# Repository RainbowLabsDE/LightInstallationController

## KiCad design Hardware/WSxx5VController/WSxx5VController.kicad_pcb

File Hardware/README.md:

# LightInstallationController

Hardware noch in Entstehung keins der boardsa ktuell in betrieb genommen.

## Main Controller

- STM32
- 8x RS485 Out
- Ethernet 
- Oled
- User Input Button / rotery Encoder ?
- Power Input 
- Digital Out to Control External Power Supply

## StripController

- CH32V003
- 5x 10A N-Channel Mosfet Output
- 5-24V Input DCDC Converter
- RS485 Tranciver

## CCController

- CH32V003 
- 5x DCDC buck CC Outputs
- 5-24V Input DCDC Converter
- RS485 Tranciver

## WSxxController

- CH32V003
- 5-24V Input DCDC Converter
- RS485 Tranciver
- P-Channel Fet to PowerOff WsxxLeds

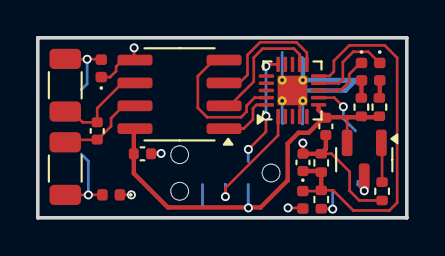
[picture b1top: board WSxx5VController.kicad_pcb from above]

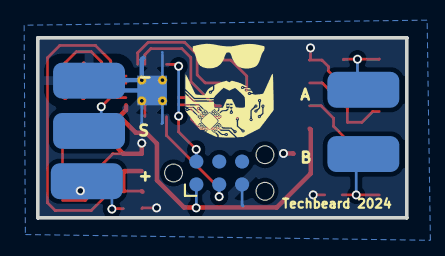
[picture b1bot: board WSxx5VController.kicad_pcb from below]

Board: 2 copper layers, 20.5 x 10.0 mm, 25 parts (6 on the bottom side), 20 nets.

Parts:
C3, C4, C5: 100n; C_0402_1005Metric
D2: 5,1V; D_0402_1005Metric
D3: S1; LED_0402_1005Metric
D4: S2; LED_0402_1005Metric
D5, D6: D_TVS; D_0402_1005Metric
IC1: CH32V003F4U6; QFN-20-1EP_3x3mm_P0.4mm_EP1.65x1.65mm_ThermalVias
J1: TagConnect; Tag-Connect_TC2030-IDC-NL_2x03_P1.27mm_Vertical
J2, J3, J4, J5, J6: Conn_01x01_Socket; SolderWirePad_1x01_SMD_2x4mm
Q1: AO3401A; SOT-23
R1: 1M; R_0402_1005Metric
R2: 270k; R_0402_1005Metric
R4, R5: 1k; R_0402_1005Metric
R6: 120; C_0402_1005Metric
R8: 100k; R_0402_1005Metric
R9, R10: 10; R_1206_3216Metric
U1: MAX485E; SOIC-8_3.9x4.9mm_P1.27mm

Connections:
+5V: C3.1, C5.1, IC1.6 (VDD), J1.1, Q1.2 (S), R4.1, R5.1, U1.8 (VCC)
A: R6.2, R10.1, U1.6 (A)
B: R6.1, R9.1, U1.7 (B)
GND: C3.2, C4.2, C5.2, D2.2 (A), D5.1 (A1), D6.1 (A1), IC1.4 (Vss), IC1.21 (Vss_Pad), J1.5, J3.1, R2.2, R8.2, U1.5 (GND)
NRST: IC1.1 (PD7/NRST), J1.3
unnamed: D3.2 (A), R4.2
unnamed: D4.2 (A), R5.2
unnamed: D5.2 (A2), J4.1, R9.2
unnamed: D6.2 (A2), J5.1, R10.2
unnamed: Q1.1 (G), R8.1
SWD: IC1.15 (PD1), J1.2
StateLed0: D4.1 (K), IC1.8 (PC1)
StateLed1: D3.1 (K), IC1.9 (PC2)
U2_DE: IC1.11 (PC4), U1.3 (DE)
U2_DI: IC1.19 (PD5), U1.4 (DI)
U2_RE: IC1.12 (PC5), U1.2 (~RE)
U2_RO: IC1.20 (PD6), U1.1 (RO)
VCC: J2.1, Q1.3 (D), R1.1
Voltage: C4.1, D2.1 (K), IC1.10 (PC3), R1.2, R2.1
WSxx: IC1.7 (PC0), J6.1

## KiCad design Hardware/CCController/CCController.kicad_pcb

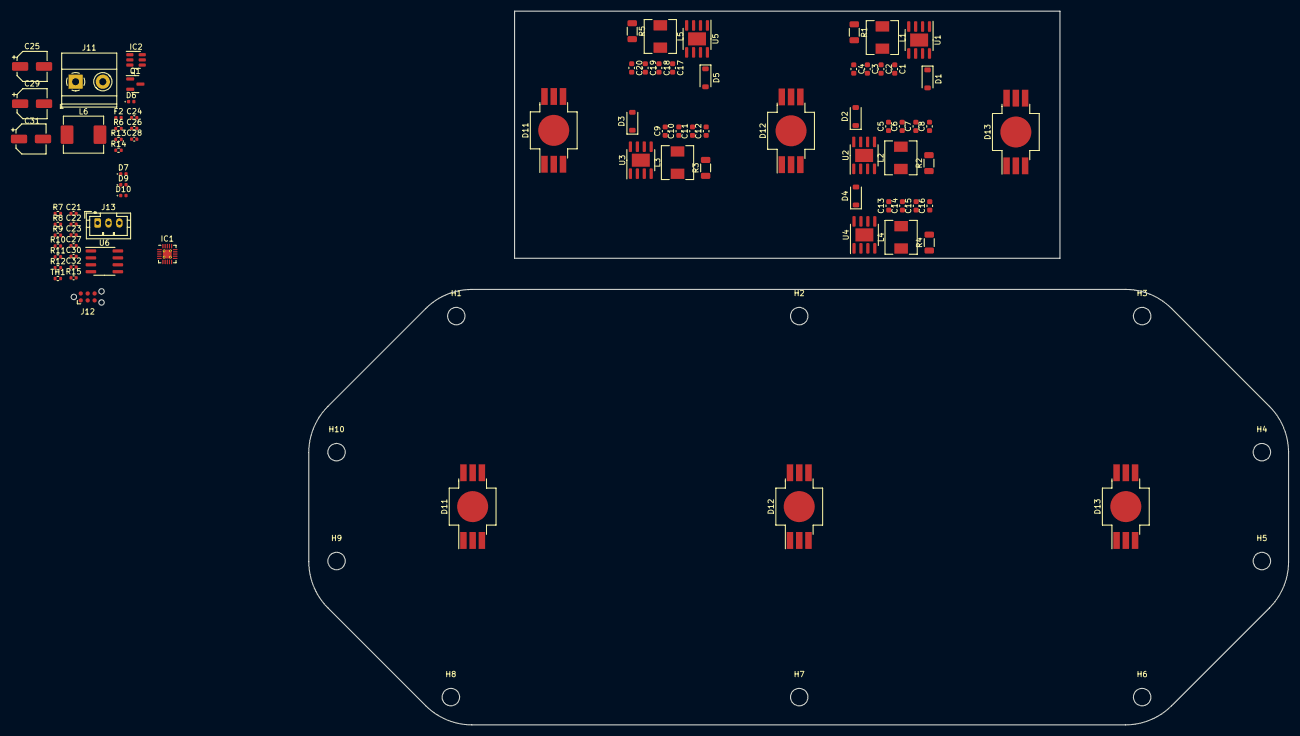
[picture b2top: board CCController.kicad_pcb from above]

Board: 2 copper layers, 180.0 x 131.1 mm, 92 parts (0 on the bottom side), 55 nets, no tracks yet.

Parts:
C1, C5, C9, C13, C17: 1n; C_0603_1608Metric
C2, C4, C6, C8, C10, C12, C14, C16, C18, C20: 1u; C_0603_1608Metric
C3, C7, C11, C15, C19: 4u7; C_0603_1608Metric
C21, C22: C; C_0402_1005Metric
C23, C24, C26, C27, C28, C30, C32: 100n; C_0402_1005Metric
C25: 47u; CP_Elec_5x5.4
C29, C31: 22u; CP_Elec_5x5.4
D1, D2, D3, D4, D5: 40V 1A Schottky; D_SOD-123
D6: 15V; D_0402_1005Metric
D7, D9, D10: LED; LED_0402_1005Metric
D11, D11#2, D12, D12#2, D13, D13#2: LED_RGB; LED_RGB_Getian_GT-P6PRGB4303
F2: 0,2A; Fuse_0402_1005Metric
H1, H2, H3, H4, H5, H6, H7, H8, H9, H10: MountingHole; MountingHole_3.2mm_M3
IC1: CH32V003F4U6; QFN-20-1EP_3x3mm_P0.4mm_EP1.65x1.65mm_ThermalVias
IC2: RY8310; SOT-23-6
J11: Conn_01x02_Pin; TerminalBlock_Phoenix_MKDS-1,5-2_1x02_P5.00mm_Horizontal
J12: TagConnect; Tag-Connect_TC2030-IDC-NL_2x03_P1.27mm_Vertical
J13: Conn_01x03_Socket; JST_PH_B3B-PH-K_1x03_P2.00mm_Vertical
L1, L2, L3, L4, L5: 10u; L_Chilisin_BMRA00050520
L6: 4.7u; L_Abracon_ASPI-0630LR
Q1: AO3401A; SOT-23
R1, R2, R3, R4, R5: 0R68; R_1206_3216Metric
R6, R11: 100k; R_0402_1005Metric
R7: 1M; R_0402_1005Metric
R8: 270k; R_0402_1005Metric
R9, R10, R12: 1k; R_0402_1005Metric
R13: 52.50 k; R_0402_1005Metric
R14: 10k; R_0402_1005Metric
R15: 1k; C_0402_1005Metric
TH1: Thermistor_NTC; R_0402_1005Metric
U1, U2, U3, U4, U5: BP1808; SOIC-8-1EP_3.9x4.9mm_P1.27mm_EP2.41x3.3mm
U6: MAX485E; SOIC-8_3.9x4.9mm_P1.27mm

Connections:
+5V: C23.1, C28.1, C29.1, C31.1, C32.1, IC1.6 (VDD), J12.1, L6.2, R9.1, R10.1, R11.1, R12.1, R13.2, U6.8 (VCC)
A+: R5.2, U5.8 (CS)
A-: C20.1, L5.2
B: IC1.7 (PC0), U3.3 (DIM)
B+: R3.2, U3.8 (CS)
B-: C12.1, L3.2
G: IC1.14 (PC7), U2.3 (DIM)
G+: R2.2, U2.8 (CS)
G-: C8.1, L2.2
GND: C1.2, C2.2, C3.2, C5.2, C6.2, C7.2, C9.2, C10.2, C11.2, C13.2, C14.2, C15.2, C17.2, C18.2, C19.2, C21.2, C22.2, C23.2, C24.2, C25.2, C27.2, C28.2, C29.2, C30.2, C31.2, C32.2, D7.1 (K), IC1.4 (Vss), IC1.21 (Vss_Pad), IC2.2 (GND), J11.2, J12.5, J13.3, R6.2, R8.2, R14.1, TH1.2, U1.4 (GND), U2.4 (GND), U3.4 (GND), U4.4 (GND), U5.4 (GND), U6.5 (GND)
NRST: IC1.1 (PD7/NRST), J12.3
unnamed: D1.2 (A), L1.1, U1.5 (SW)
unnamed: D2.2 (A), L2.1, U2.5 (SW)
unnamed: D3.2 (A), L3.1, U3.5 (SW)
unnamed: D4.2 (A), L4.1, U4.5 (SW)
unnamed: D5.2 (A), L5.1, U5.5 (SW)
unnamed: D6.2 (A), Q1.1 (G), R6.1
unnamed: C24.1, C25.1, D6.1 (K), IC2.4 (EN), IC2.5 (IN), Q1.2 (S)
unnamed: D7.2 (A), R9.2
unnamed: D9.2 (A), R10.2
unnamed: D10.2 (A), R12.2
unnamed: C26.1, IC2.1 (CB)
unnamed: IC2.3 (FB), R13.1, R14.2
unnamed: C26.2, IC2.6 (SW), L6.1
unnamed: F2.1, J11.1
unnamed: F2.2, Q1.3 (D)
unnamed: C1.1, U1.2 (COMP)
unnamed: C2.1, U1.6 (VDD)
unnamed: C5.1, U2.2 (COMP)
unnamed: C6.1, U2.6 (VDD)
unnamed: C9.1, U3.2 (COMP)
unnamed: C10.1, U3.6 (VDD)
unnamed: C13.1, U4.2 (COMP)
unnamed: C14.1, U4.6 (VDD)
unnamed: C17.1, U5.2 (COMP)
unnamed: C18.1, U5.6 (VDD)
R: IC1.13 (PC6), U1.3 (DIM)
R+: R1.2, U1.8 (CS)
R-: C4.1, L1.2
RA: J13.1, R15.2, U6.6 (A)
RB: J13.2, R15.1, U6.7 (B)
SWD: IC1.15 (PD1), J12.2
StateLed0: D10.1 (K), IC1.8 (PC1)
StateLed1: D9.1 (K), IC1.9 (PC2)
Temp: C30.1, IC1.16 (PD2), R11.2, TH1.1
U2_DE: IC1.11 (PC4), U6.3 (DE)
U2_DI: IC1.19 (PD5), U6.4 (DI)
U2_RE: IC1.12 (PC5), U6.2 (~RE)
U2_RO: IC1.20 (PD6), U6.1 (RO)
VCC: C3.1, C4.2, C7.1, C8.2, C11.1, C12.2, C15.1, C16.2, C19.1, C20.2, D1.1 (K), D2.1 (K), D3.1 (K), D4.1 (K), D5.1 (K), R1.1, R2.1, R3.1, R4.1, R5.1, R7.1, U1.7 (VOUT), U2.7 (VOUT), U3.7 (VOUT), U4.7 (VOUT), U5.7 (VOUT)
Voltage: C27.1, IC1.10 (PC3), R7.2, R8.1
W: IC1.17 (PD3), U4.3 (DIM)
W+: R4.2, U4.8 (CS)
W-: C16.1, L4.2
WW: IC1.18 (PD4), U5.3 (DIM)

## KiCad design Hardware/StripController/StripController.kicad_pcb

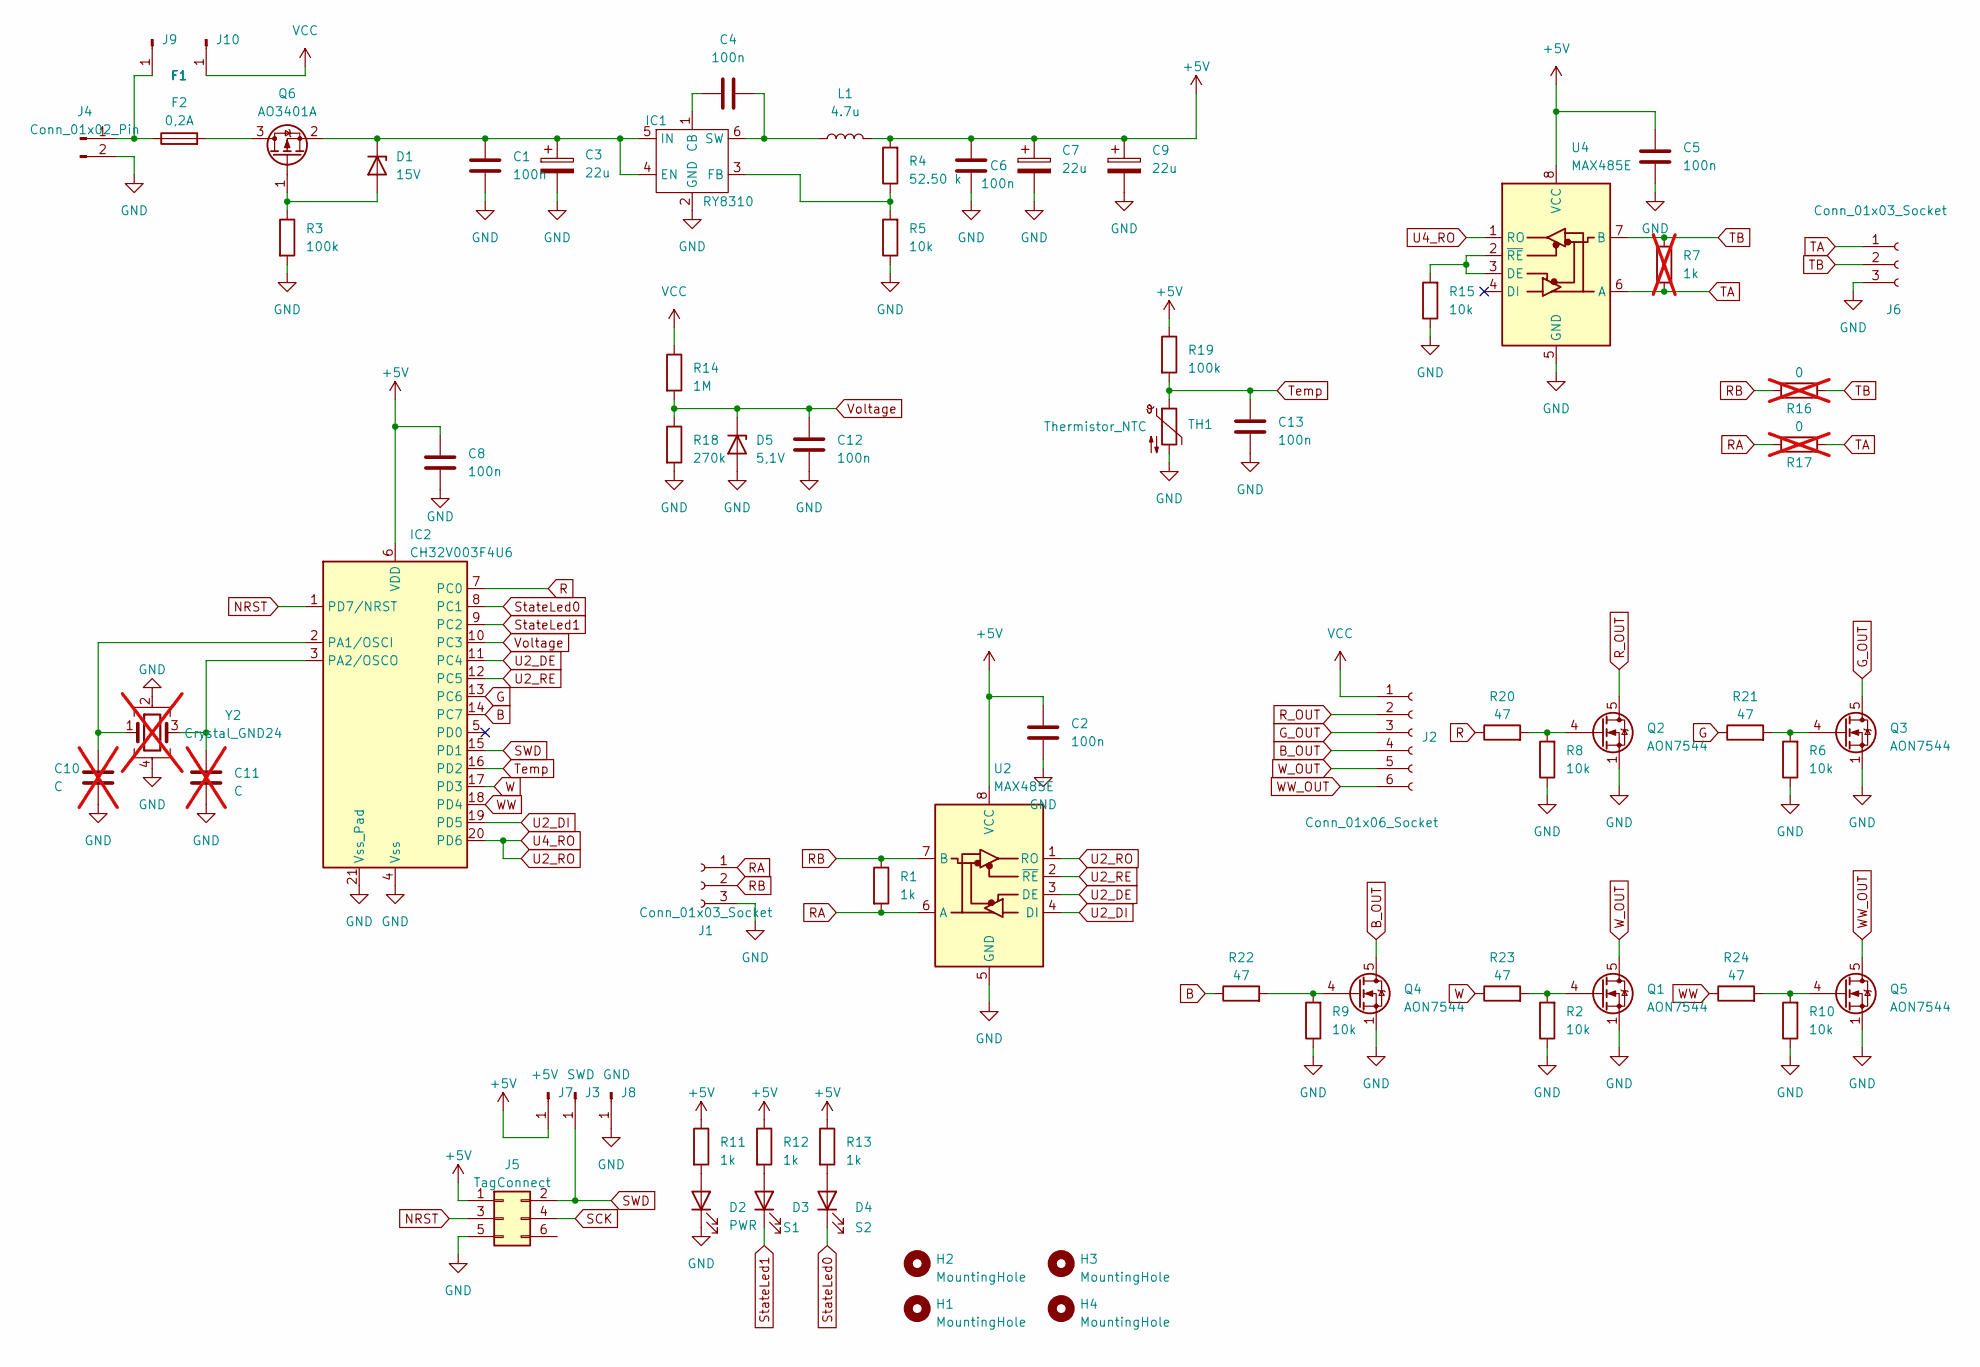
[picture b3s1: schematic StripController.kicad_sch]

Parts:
C1, C2, C4, C5, C6, C8, C12, C13: 100n; C_0402_1005Metric
C3, C7, C9: 22u; CP_Elec_5x5.4
C10, C11: C; C_0402_1005Metric; not fitted
D1: 15V; D_SOD-323
D2: PWR; LED_0603_1608Metric
D3: S1; LED_0603_1608Metric
D4: S2; LED_0603_1608Metric
D5: 5,1V; D_SOD-323
F2: 0,2A; Fuse_0402_1005Metric
H1, H2, H3, H4: MountingHole; MountingHole_3.2mm_M3
IC1: RY8310; SOT-23-6
IC2: CH32V003F4U6; QFN-20-1EP_3x3mm_P0.4mm_EP1.65x1.65mm_ThermalVias
J1, J6: Conn_01x03_Socket; JST_PH_B3B-PH-K_1x03_P2.00mm_Vertical
J2: Conn_01x06_Socket; TerminalBlock_Phoenix_MKDS-1,5-6_1x06_P5.00mm_Horizontal
J3: SWD; TestPoint_Pad_1.5x1.5mm
J4: Conn_01x02_Pin; TerminalBlock_Phoenix_MKDS-1,5-2_1x02_P5.00mm_Horizontal
J5: TagConnect; Tag-Connect_TC2030-IDC-NL_2x03_P1.27mm_Vertical
J7: +5V; TestPoint_Pad_1.5x1.5mm
J8: GND; TestPoint_Pad_1.5x1.5mm
J9, J10: F1; Fuseholder C3130
L1: 4.7u; L_0630
Q1, Q2, Q3, Q4, Q5: AON7544
Q6: AO3401A; TSOT-23
R1: 1k; C_0402_1005Metric
R2, R5, R6, R8, R9, R10, R15: 10k; R_0402_1005Metric
R3, R19: 100k; R_0402_1005Metric
R4: 52.50 k; R_0402_1005Metric
R7: 1k; C_0402_1005Metric; not fitted
R11, R12, R13: 1k; R_0402_1005Metric
R14: 1M; R_0402_1005Metric
R16, R17: 0; R_0402_1005Metric; not fitted
R18: 270k; R_0402_1005Metric
R20, R21, R22, R23, R24: 47; R_0402_1005Metric
TH1: Thermistor_NTC; R_0402_1005Metric
U2, U4: MAX485E; SOIC-8_3.9x4.9mm_P1.27mm
Y2: Crystal_GND24; Crystal_SMD_3225-4Pin_3.2x2.5mm; not fitted

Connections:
B: IC2.14 (PC7), R22.1
B_OUT: J2.4, Q4.5 (D)
G: IC2.13 (PC6), R21.1
GND: C1.2, C2.2, C3.2, C5.2, C6.2, C7.2, C8.2, C9.2, C10.2, C11.2, C12.2, C13.2, D2.1 (K), D5.2 (A), IC1.2 (GND), IC2.4 (Vss), IC2.21 (Vss_Pad), J1.3, J4.2, J5.5, J6.3, J8.1, Q1.1 (S), Q1.2 (S), Q1.3 (S), Q2.1 (S), Q2.2 (S), Q2.3 (S), Q3.1 (S), Q3.2 (S), Q3.3 (S), Q4.1 (S), Q4.2 (S), Q4.3 (S), Q5.1 (S), Q5.2 (S), Q5.3 (S), R2.1, R3.2, R5.1, R6.1, R8.1, R9.1, R10.1, R15.1, R18.2, TH1.2, U2.5 (GND), U4.5 (GND), Y2.2, Y2.4
G_OUT: J2.3, Q3.5 (D)
NRST: IC2.1 (PD7/NRST), J5.3
unnamed: D1.2 (A), Q6.1 (G), R3.1
unnamed: C1.1, C3.1, D1.1 (K), IC1.4 (EN), IC1.5 (IN), Q6.2 (S)
unnamed: D2.2 (A), R11.2
unnamed: D3.2 (A), R12.2
unnamed: D4.2 (A), R13.2
unnamed: C4.1, IC1.1 (CB)
unnamed: IC1.3 (FB), R4.1, R5.2
unnamed: C4.2, IC1.6 (SW), L1.1
unnamed: C10.1, IC2.2 (PA1/OSCI), Y2.1
unnamed: C11.1, IC2.3 (PA2/OSCO), Y2.3
unnamed: F2.1, J4.1, J9.1
unnamed: Q1.4 (G), R2.2, R23.2
unnamed: Q2.4 (G), R8.2, R20.2
unnamed: Q3.4 (G), R6.2, R21.2
unnamed: Q4.4 (G), R9.2, R22.2
unnamed: Q5.4 (G), R10.2, R24.2
unnamed: F2.2, Q6.3 (D)
unnamed: R15.2, U4.2 (~RE), U4.3 (DE)
R: IC2.7 (PC0), R20.1
RA: J1.1, R1.2, R17.1, U2.6 (A)
RB: J1.2, R1.1, R16.2, U2.7 (B)
R_OUT: J2.2, Q2.5 (D)
SCK: J5.4
SWD: IC2.15 (PD1), J3.1, J5.2
StateLed0: D4.1 (K), IC2.8 (PC1)
StateLed1: D3.1 (K), IC2.9 (PC2)
TA: J6.1, R7.2, R17.2, U4.6 (A)
TB: J6.2, R7.1, R16.1, U4.7 (B)
Temp: C13.1, IC2.16 (PD2), R19.2, TH1.1
U2_DE: IC2.11 (PC4), U2.3 (DE)
U2_DI: IC2.19 (PD5), U2.4 (DI)
U2_RE: IC2.12 (PC5), U2.2 (~RE)
U2_RO: IC2.20 (PD6), U2.1 (RO), U4.1 (RO)
W: IC2.17 (PD3), R23.1
WW: IC2.18 (PD4), R24.1
WW_OUT: J2.6, Q5.5 (D)
W_OUT: J2.5, Q1.5 (D)

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
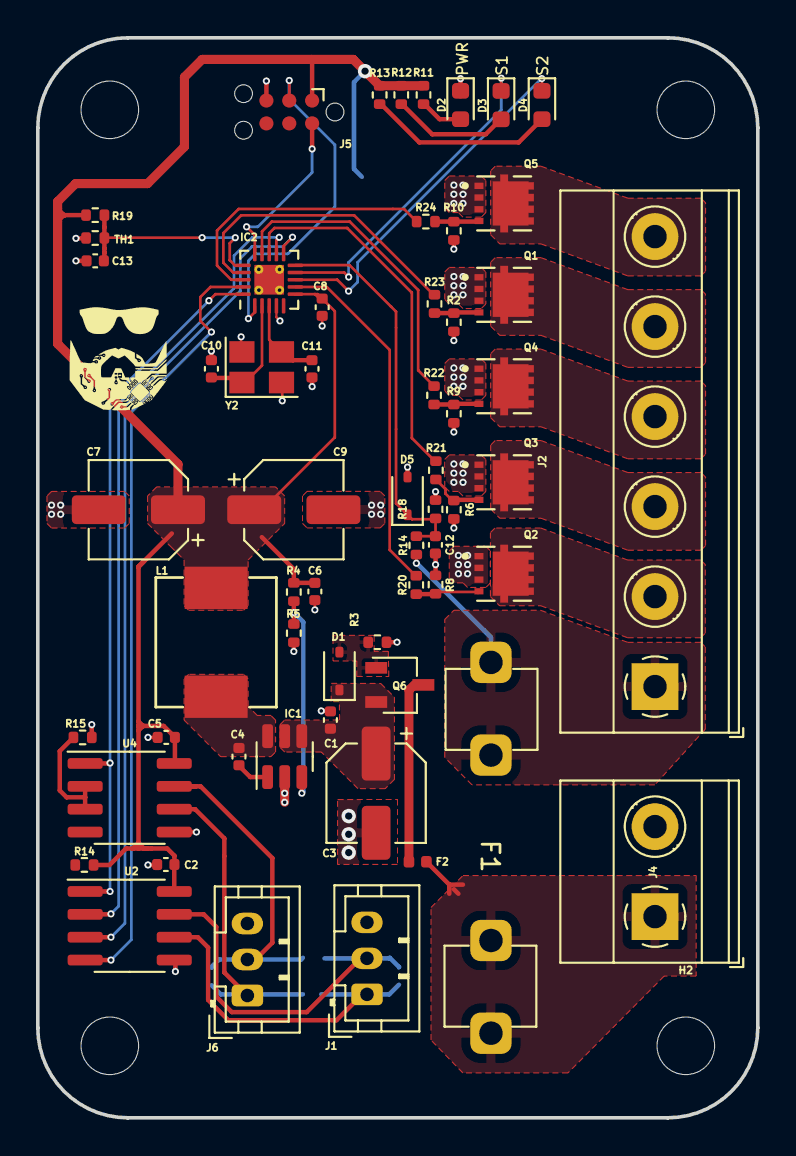
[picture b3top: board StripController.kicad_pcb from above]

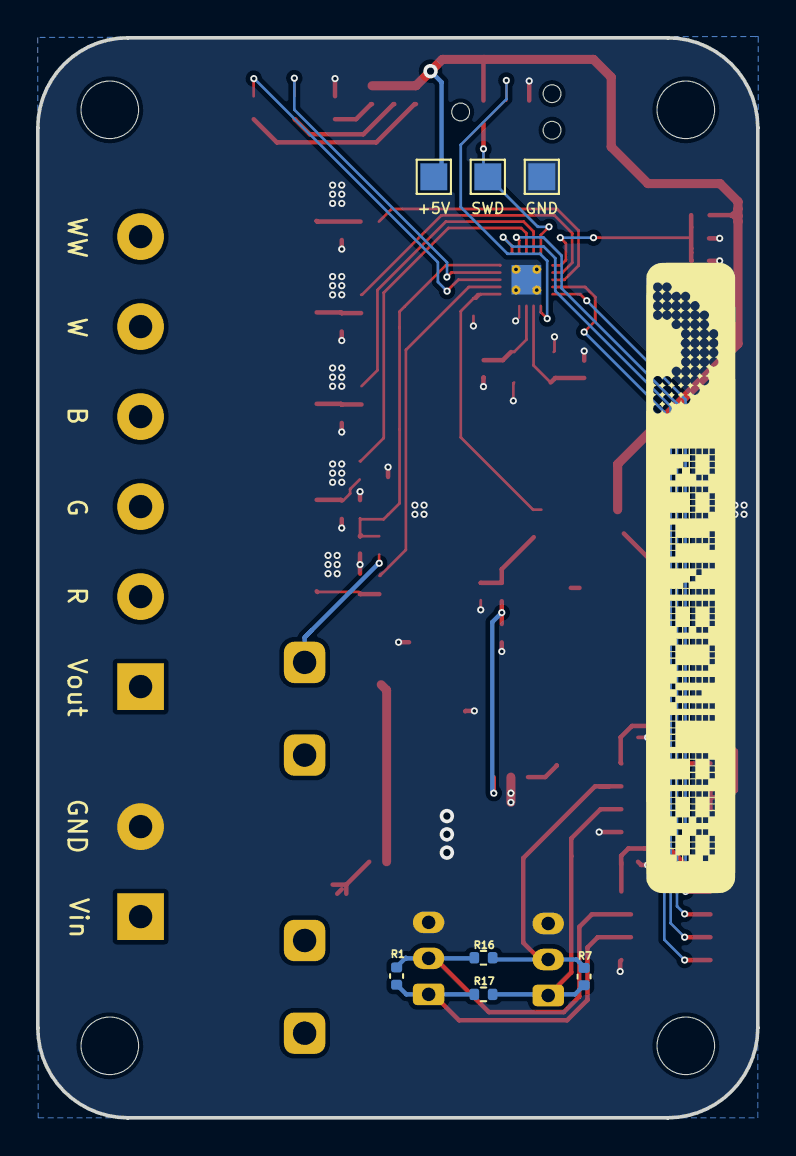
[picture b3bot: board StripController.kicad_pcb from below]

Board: 2 copper layers, 40.0 x 60.0 mm, 71 parts (7 on the bottom side), 45 nets.

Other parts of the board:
R14#2: 1M; R_0402_1005Metric

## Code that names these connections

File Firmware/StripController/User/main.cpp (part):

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vu8 val;
Config config;

// R  - T1CH3 - PC0
// G  - T1CH1 - PC6 | WS2812 DOUT
// B  - T1CH2 - PC7
// W  - T1CH4 - PD3
// WW - T2CH2 - PD4
// TX - PD5
// RX - PD6
// LED1 - PC1
// LED2 - PC2
// DE - PC4
// RE - PC5 (active low)
// VBUS - PC3 - A?? (wrong pin?) -> PA2 (A0)
// TEMP - PD2 - A3

#define PIN_LED1        GPIOC, GPIO_Pin_1
#define PIN_LED2        GPIOC, GPIO_Pin_2
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 */
void TIM1_PWMOut_Init(u16 arr, u16 psc, u16 ccp) {
    RCC_APB2PeriphClockCmd(RCC_APB2Periph_AFIO, ENABLE);
    GPIO_PinRemapConfig(GPIO_PartialRemap1_TIM1, ENABLE); // CH1-4: PC6, PC7, PC0, PD3

    GPIO_InitTypeDef GPIO_InitStructure = {0};
    TIM_OCInitTypeDef TIM_OCInitStructure = {0};
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
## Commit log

2023-02-15 add Hardware files
2023-02-15 initialize CH32V003 MounRiver project
2023-02-15 add PWM example
2023-02-15 enable other 3 PWM channels on TIM1 and remap pins
    Remapping doesn't work for some reason, still outputting on default pins
2023-02-15 fix pin remapping (AFIO clk needs to be enabled)
2023-02-15 test reading chip UID
2023-02-16 convert project to C++
2023-02-16 add FW/SC readme
2023-02-16 begin implementing UART DMA
2023-02-16 move UART to separate file
    the structure doesn't quite feel right tho
2023-02-16 implement better SysTick timing functions
2023-02-16 try to optimize calculation time of micros()
    but there is another multiply which I can't easily get rid of
2023-02-16 fix longer delays not working
2023-02-16 implement getUID
2023-02-20 edit pcb desine
2023-02-26 add CCController
2023-03-07 UART implement readBytes
2023-03-07 begin with UART protocol implementation
    WIP, not working
2023-03-10 dry-implement more of the RBLB protocol
2023-03-11 edit Strip controller and buy first batch
2023-03-23 GPIO config and further RBLB development
2023-03-24 implement ADC DMA reading
2023-04-06 add code for test host for RBLB
2023-04-06 basic communication between RBLB host and nodes
2023-04-06 fix host not receiving packets
2023-08-07 auto discovery proof of concept working
2023-11-01 fix discovery algorithm
2023-11-01 fix RS485 not working (GPIOs not initialized)
2024-04-03 implement building via PlatformIO
2024-04-03 implement config storage in custom user option bytes
2024-04-04 add ability to disable debug prints
2024-04-05 add Files
2024-04-06 add buffer in preparation for data reception
2024-04-18 implement UID data command
2024-04-18 implement bit depth config
2024-04-18 implement simple data protocol
2024-04-23 add CNLohr WS2812 library
2024-04-23 implement WS2812 output
2024-04-23 begin optimizing serial handling
    improved from ~1.5Mbaud to ~2.5MBaud capable, still not quite at 3
2024-04-23 optimize protocol parsing so 3MBaud is working with WS2812 output
2024-08-02 fix discovery being broken
    buffer was marked as empty too soon, but discovery relied on buffer being non-empty to detect collision
2024-08-03 fix MainController crashing on DataSimple transmit (while also receiving)
2024-08-03 StripController PWM test successful
2024-08-03 fix some compile warnings
2024-08-04 move Host handlePacketInternal() to Host class
2024-08-05 begin playing around with possible bootloader implementation
